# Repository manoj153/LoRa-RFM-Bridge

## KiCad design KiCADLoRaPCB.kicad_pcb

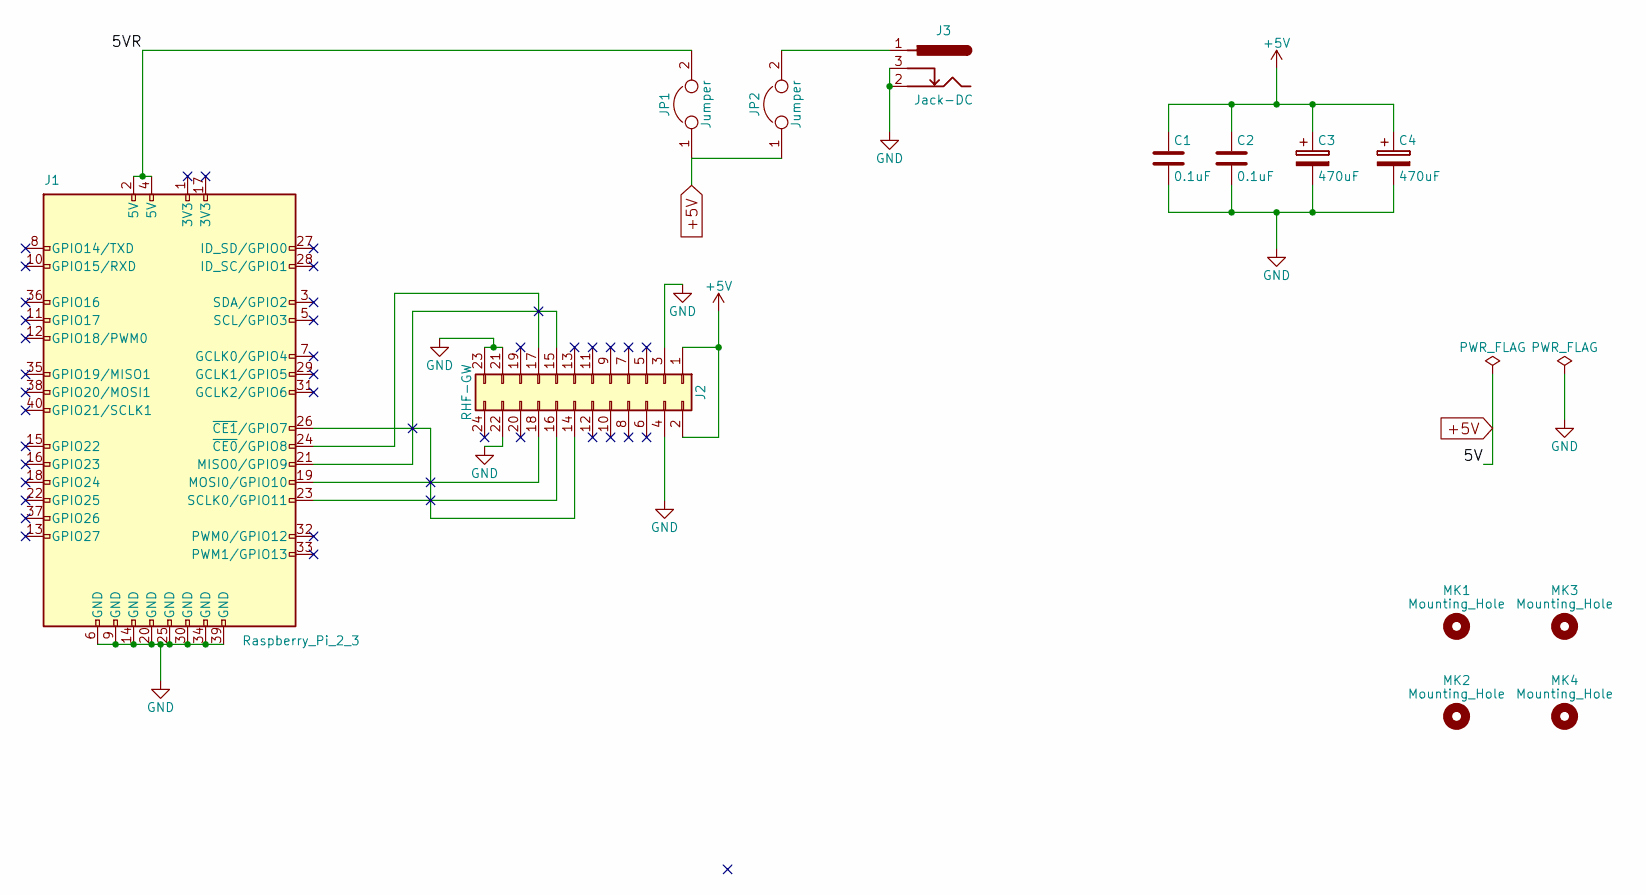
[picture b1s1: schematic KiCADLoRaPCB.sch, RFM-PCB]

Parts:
C1, C2: 0.1uF; C_0805_2012Metric_Pad1.29x1.40mm_HandSolder
C3, C4: 470uF; CP_EIA-7343-40_Kemet-Y_Pad2.23x2.60mm_HandSolder
J1: Raspberry_Pi_2_3; PinSocket_2x20_P2.54mm_Vertical
J2: RHF-GW; PinSocket_2x12_P2.54mm_Vertical
J3: Jack-DC; BarrelJack_CUI_PJ-102AH_Horizontal
JP1, JP2: Jumper; PinHeader_1x02_P2.54mm_Vertical
MK1, MK2, MK3, MK4: Mounting_Hole; MountingHole_4.3mm_M4

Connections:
+5V: C1.1, C2.1, C3.1, C4.1, J2.1, J2.2, JP1.1, JP2.1
/5VR: J1.2 (5V), J1.4 (5V), JP1.2
GND: C1.2, C2.2, C3.2, C4.2, J1.6 (GND), J1.9 (GND), J1.14 (GND), J1.20 (GND), J1.25 (GND), J1.30 (GND), J1.34 (GND), J1.39 (GND), J2.3, J2.4, J2.21, J2.22, J2.23, J3.2, J3.3
unnamed: J1.19 (MOSI0/GPIO10), J2.18
unnamed: J1.21 (MISO0/GPIO9), J2.15
unnamed: J1.23 (SCLK0/GPIO11), J2.16
unnamed: J1.24 (~CE0~/GPIO8), J2.17
unnamed: J1.26 (~CE1~/GPIO7), J2.14
unnamed: J3.1, JP2.2

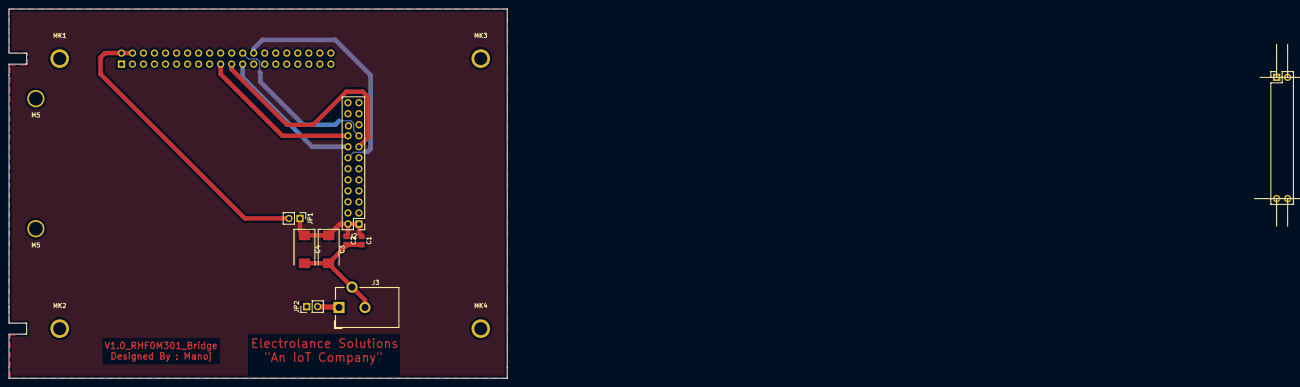
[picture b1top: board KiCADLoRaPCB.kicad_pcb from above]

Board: 2 copper layers, 114.8 x 85.1 mm, 16 parts (1 on the bottom side), 9 nets.

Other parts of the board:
J9: RHF-GWx; PinSocket_2x12_P2.54mm_Vertical
M5, M5#2: 3.2mm; MountingHole_3.2mm_M3_DIN965_Pad

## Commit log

2018-05-07 first track commit
2018-05-07 edge cut layer of the square case cut are refined mistakes
2018-05-07 All holes ext PCB alignedwith case hole
2018-05-07 cleanUps
2018-05-07 aligned the gpio pin header
2018-05-08 RisingHF board outline drawed on Cmts.User layer
2018-05-08 header risingHF pin aligned
2018-05-13 PCB done but need advise on POWER Trace
2018-05-13 added local library for DC Barrel Jack
2018-05-13 Finished tweaking the PWR plane and track width
2018-05-14 Etching round design
